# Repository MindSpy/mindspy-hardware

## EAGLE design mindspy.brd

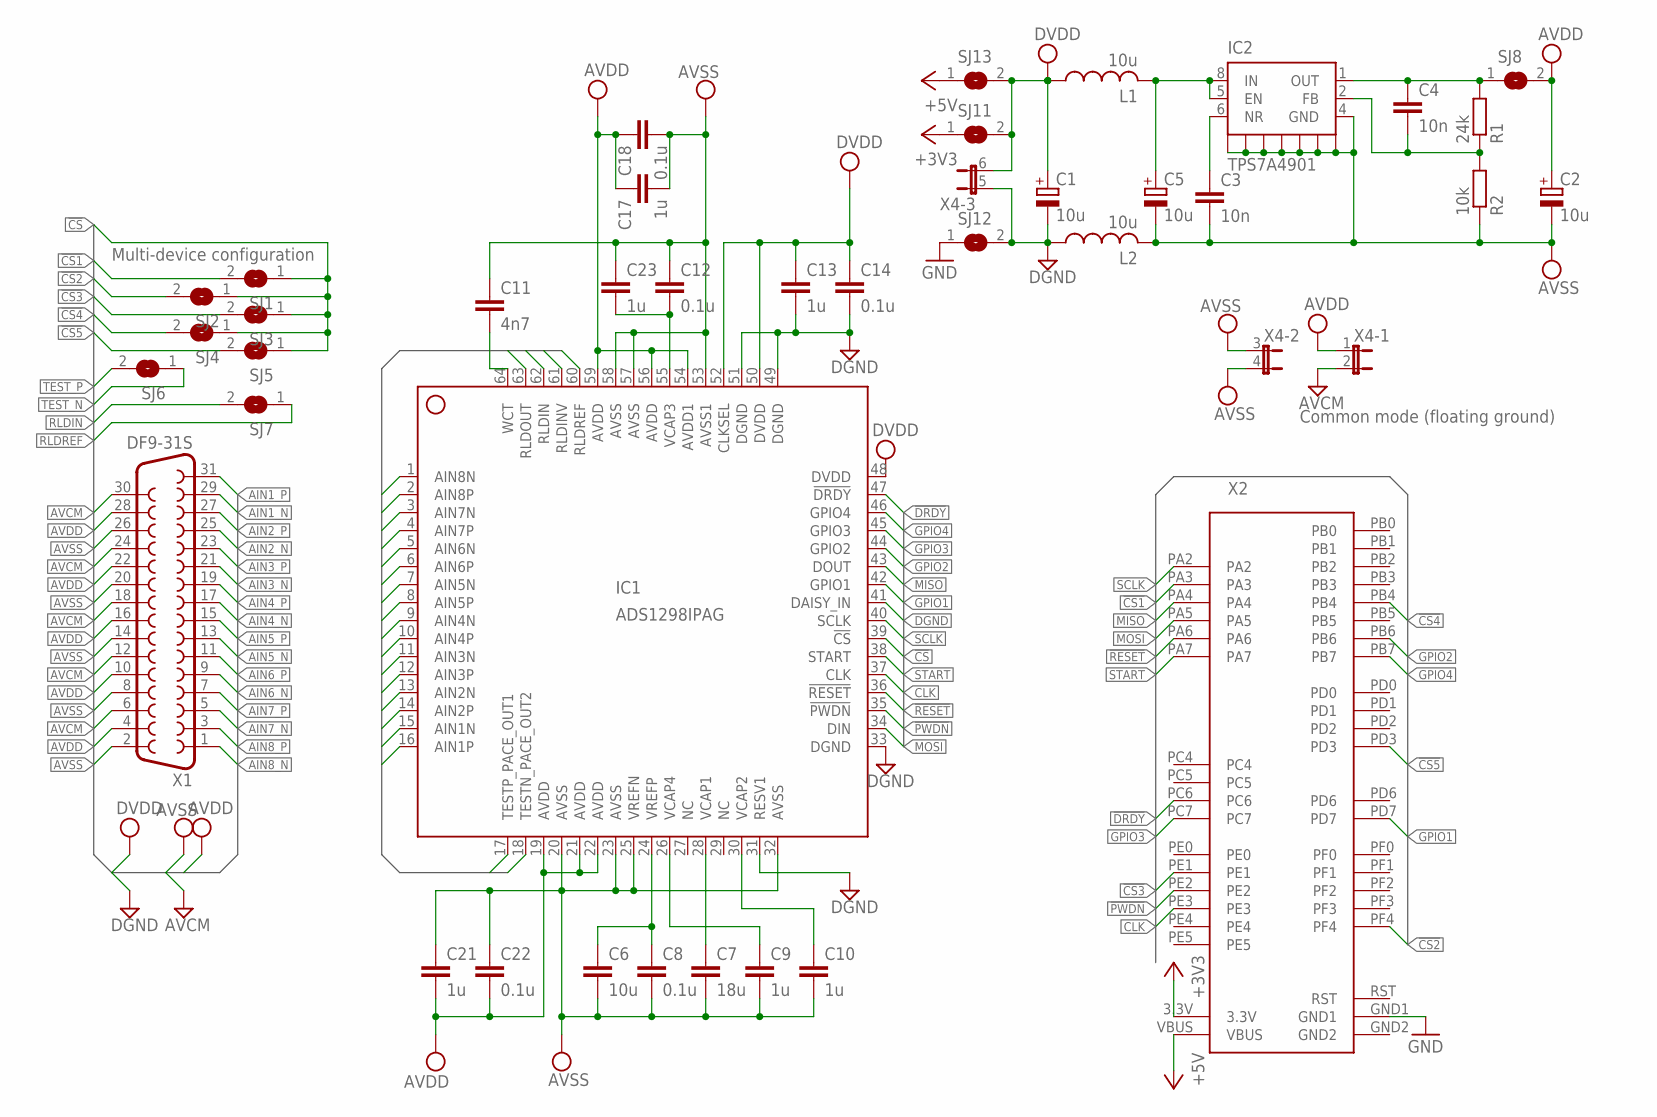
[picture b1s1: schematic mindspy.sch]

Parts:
C1, C2, C5: 10u; SMC_A
C3, C4: 10n; C0603
C6: 10u; C0805
C7: 18u; C0805
C8, C12, C14, C18, C22: 0.1u; C0402
C9, C10, C13, C17, C21, C23: 1u; C0402
C11: 4n7; C0402
IC1: ADS1298IPAG; LQFP64
IC2: TPS7A4901; MSOP08
L1, L2: 10u; L1210K
R1: 24k; R0402
R2: 10k; R0402
SJ1, SJ2, SJ3, SJ4, SJ5, SJ6, SJ7, SJ8, SJ11, SJ12, SJ13: SJ
X1: DF9-31S
X2: STELLARIS-LAUNCHPAD-HALF; LAUNCHPAD-L
X4: JP3QE; JP3Q

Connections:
!CS: IC1.39 (!CS), SJ1.1, SJ2.1, SJ3.1, SJ4.1, SJ5.1
!CS1: SJ1.2, X2.PA3
!CS2: SJ2.2, X2.PF4
!CS3: SJ3.2, X2.PE1
!CS4: SJ4.2, X2.PB4
!CS5: SJ5.2, X2.PD3
!DRDY: IC1.47 (!DRDY), X2.PC6
!PWDN: IC1.35 (!PWDN), X2.PE2
!RESET: IC1.36 (!RESET), X2.PA6
+3V3: SJ11.1, X2.3.3V
+5V: SJ13.1, X2.VBUS
AIN1_N: IC1.15 (AIN1N), X1.29
AIN1_P: IC1.16 (AIN1P), X1.31
AIN2_N: IC1.13 (AIN2N), X1.25
AIN2_P: IC1.14 (AIN2P), X1.27
AIN3_N: IC1.11 (AIN3N), X1.21
AIN3_P: IC1.12 (AIN3P), X1.23
AIN4_N: IC1.9 (AIN4N), X1.17
AIN4_P: IC1.10 (AIN4P), X1.19
AIN5_N: IC1.7 (AIN5N), X1.13
AIN5_P: IC1.8 (AIN5P), X1.15
AIN6_N: IC1.5 (AIN6N), X1.9
AIN6_P: IC1.6 (AIN6P), X1.11
AIN7_N: IC1.3 (AIN7N), X1.5
AIN7_P: IC1.4 (AIN7P), X1.7
AIN8_N: IC1.1 (AIN8N), X1.1
AIN8_P: IC1.2 (AIN8P), X1.3
AVCM: X1.6, X1.12, X1.18, X1.24, X1.30, X4.2
AVDD: C2.+, C17.1, C18.1, C21.2, C22.2, IC1.19 (AVDD), IC1.21 (AVDD), IC1.22 (AVDD), IC1.54 (AVDD1), IC1.56 (AVDD), IC1.59 (AVDD), SJ8.2, X1.4, X1.10, X1.16, X1.22, X1.28, X4.1
AVDD2: C4.1, IC2.1 (OUT), R1.2, SJ8.1
AVSS: C2.-, C3.2, C5.-, C6.2, C7.2, C8.2, C9.2, C10.2, C11.1, C12.1, C17.2, C18.2, C21.1, C22.1, C23.1, IC1.20 (AVSS), IC1.23 (AVSS), IC1.25 (VREFN), IC1.32 (AVSS), IC1.53 (AVSS1), IC1.57 (AVSS), IC1.58 (AVSS), IC2.4 (GND), IC2.NC@0 (GND), IC2.NC@1 (GND), IC2.NC@2 (GND), IC2.NC@3 (GND), IC2.NC@4 (GND), IC2.PWR@1 (GND), IC2.PWR@2 (GND), L2.2, R2.1, X1.2, X1.8, X1.14, X1.20, X1.26, X4.3 (1), X4.4 (2)
CLK: IC1.37 (CLK), X2.PE3
DGND: C1.-, C13.2, C14.2, IC1.31 (RESV1), IC1.33 (DGND), IC1.41 (DAISY_IN), IC1.49 (DGND), IC1.51 (DGND), L2.1, SJ12.2, X4.5 (1)
DVDD: C1.+, C13.1, C14.1, IC1.48 (DVDD), IC1.50 (DVDD), IC1.52 (CLKSEL), L1.1, SJ11.2, SJ13.2, X4.6 (2)
GND: SJ12.1, X2.GND1
GND2: X2.GND2
GPIO1: IC1.42 (GPIO1), X2.PD7
GPIO2: IC1.44 (GPIO2), X2.PB6
GPIO3: IC1.45 (GPIO3), X2.PC7
GPIO4: IC1.46 (GPIO4), X2.PB7
MISO: IC1.43 (DOUT), X2.PA4
MOSI: IC1.34 (DIN), X2.PA5
unnamed: C6.1, C8.1, IC1.24 (VREFP)
unnamed: C7.1, IC1.28 (VCAP1)
unnamed: C3.1, IC2.6 (NR)
unnamed: C9.1, IC1.26 (VCAP4)
unnamed: C10.1, IC1.30 (VCAP2)
unnamed: C12.2, C23.2, IC1.55 (VCAP3)
unnamed: C11.2, IC1.64 (WCT)
unnamed: C4.2, IC2.2 (FB), R1.1, R2.2
unnamed: C5.+, IC2.5 (EN), IC2.8 (IN), L1.2
RLDIN: IC1.62 (RLDIN), SJ7.2
RLDINV: IC1.61 (RLDINV)
RLDOUT: IC1.63 (RLDOUT)
RLDREF: IC1.60 (RLDREF), SJ7.1
RST: X2.RST
SCLK: IC1.40 (SCLK), X2.PA2
START: IC1.38 (START), X2.PA7
TEST_N: IC1.18 (TESTN_PACE_OUT2), SJ6.1
TEST_P: IC1.17 (TESTP_PACE_OUT1), SJ6.2

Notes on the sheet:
Common mode (floating ground)
Multi-device configuration

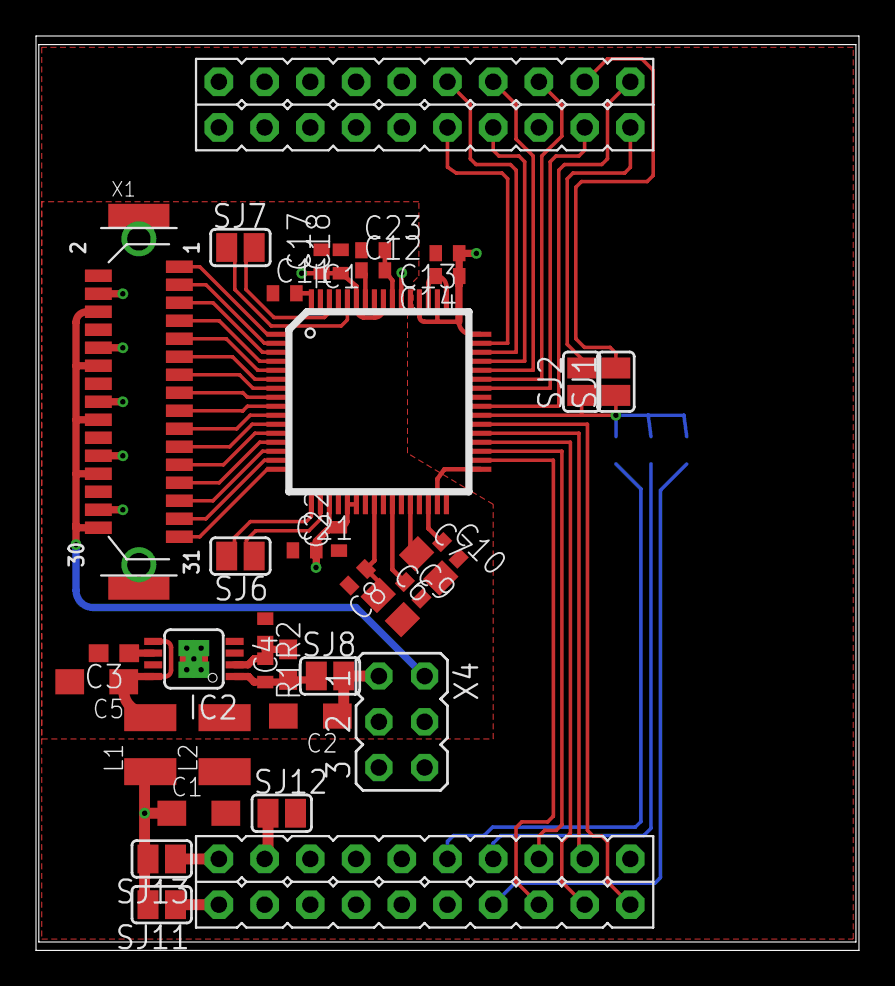
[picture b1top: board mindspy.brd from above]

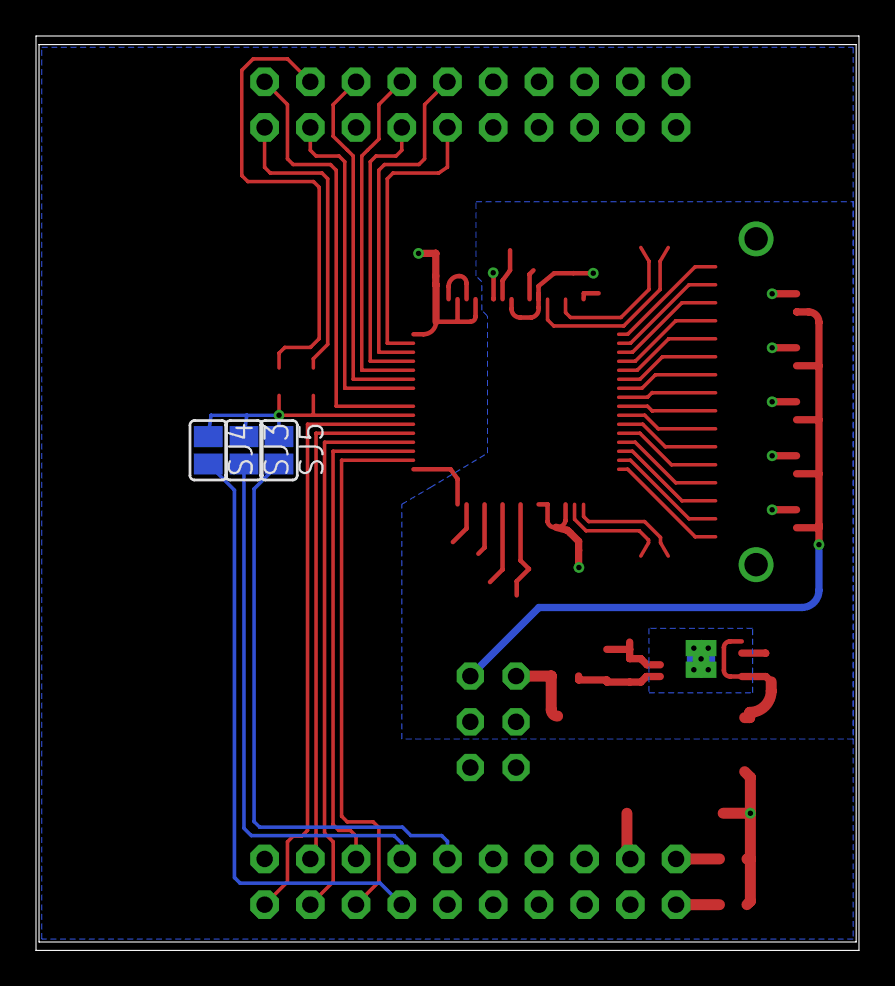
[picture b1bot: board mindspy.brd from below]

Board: 2 copper layers, 45.7 x 50.8 mm, 39 parts (3 on the bottom side), 56 nets.

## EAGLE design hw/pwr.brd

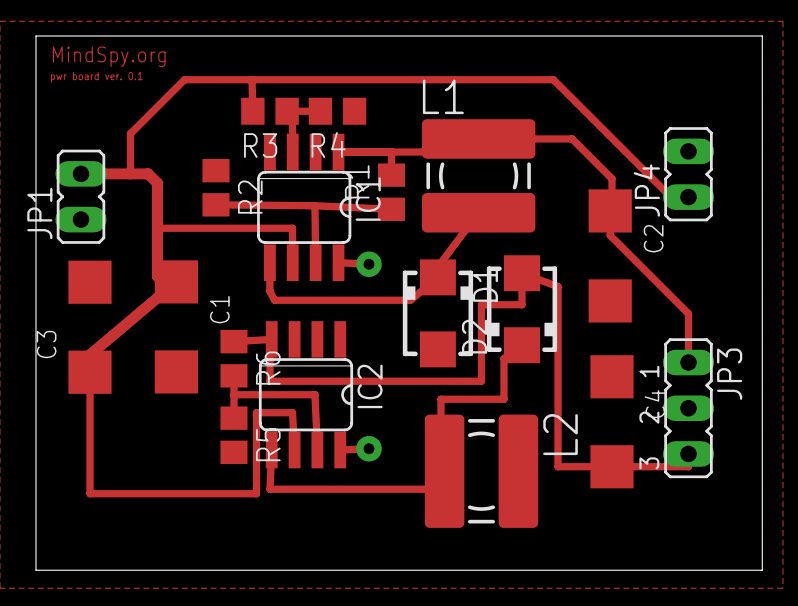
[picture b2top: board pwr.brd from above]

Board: 2 copper layers, 40.4 x 29.7 mm, 19 parts (0 on the bottom side), 10 nets.

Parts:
C1, C3: 33u; SMC_C
C2, C4: 100u; SMC_C
D1, D2: SS14; SMA
IC1, IC2: MAX640; SO08
JP1: BATT; JP1
JP3: ANAL; JP2
JP4: DIGI; JP1
L1, L2: POWER-CHOKE_WE-TPC
R1, R2, R3, R4, R5, R6: R0805

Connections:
+2V5: C2.+, IC1.1, JP3.1, L1.1, R1.2
-2V5: C4.-, D2.A, IC2.4, JP3.3, R6.1
GND: C1.-, C2.-, C3.-, C4.+, D1.A, IC1.4, IC2.1, IC2.3, JP1.1, JP3.2, JP4.2, L2.1, R2.1, R4.1, R5.2
unnamed: D1.C, IC1.5, L1.2
unnamed: D2.C, IC2.5, L2.2
unnamed: IC1.3, R3.1, R4.2
unnamed: IC1.7, R1.1, R2.2
unnamed: IC2.7, R5.1, R6.2
SHDN: IC1.8, IC2.8
VBAT: C1.+, C3.+, IC1.6, IC2.6, JP1.2, JP4.1, R3.2

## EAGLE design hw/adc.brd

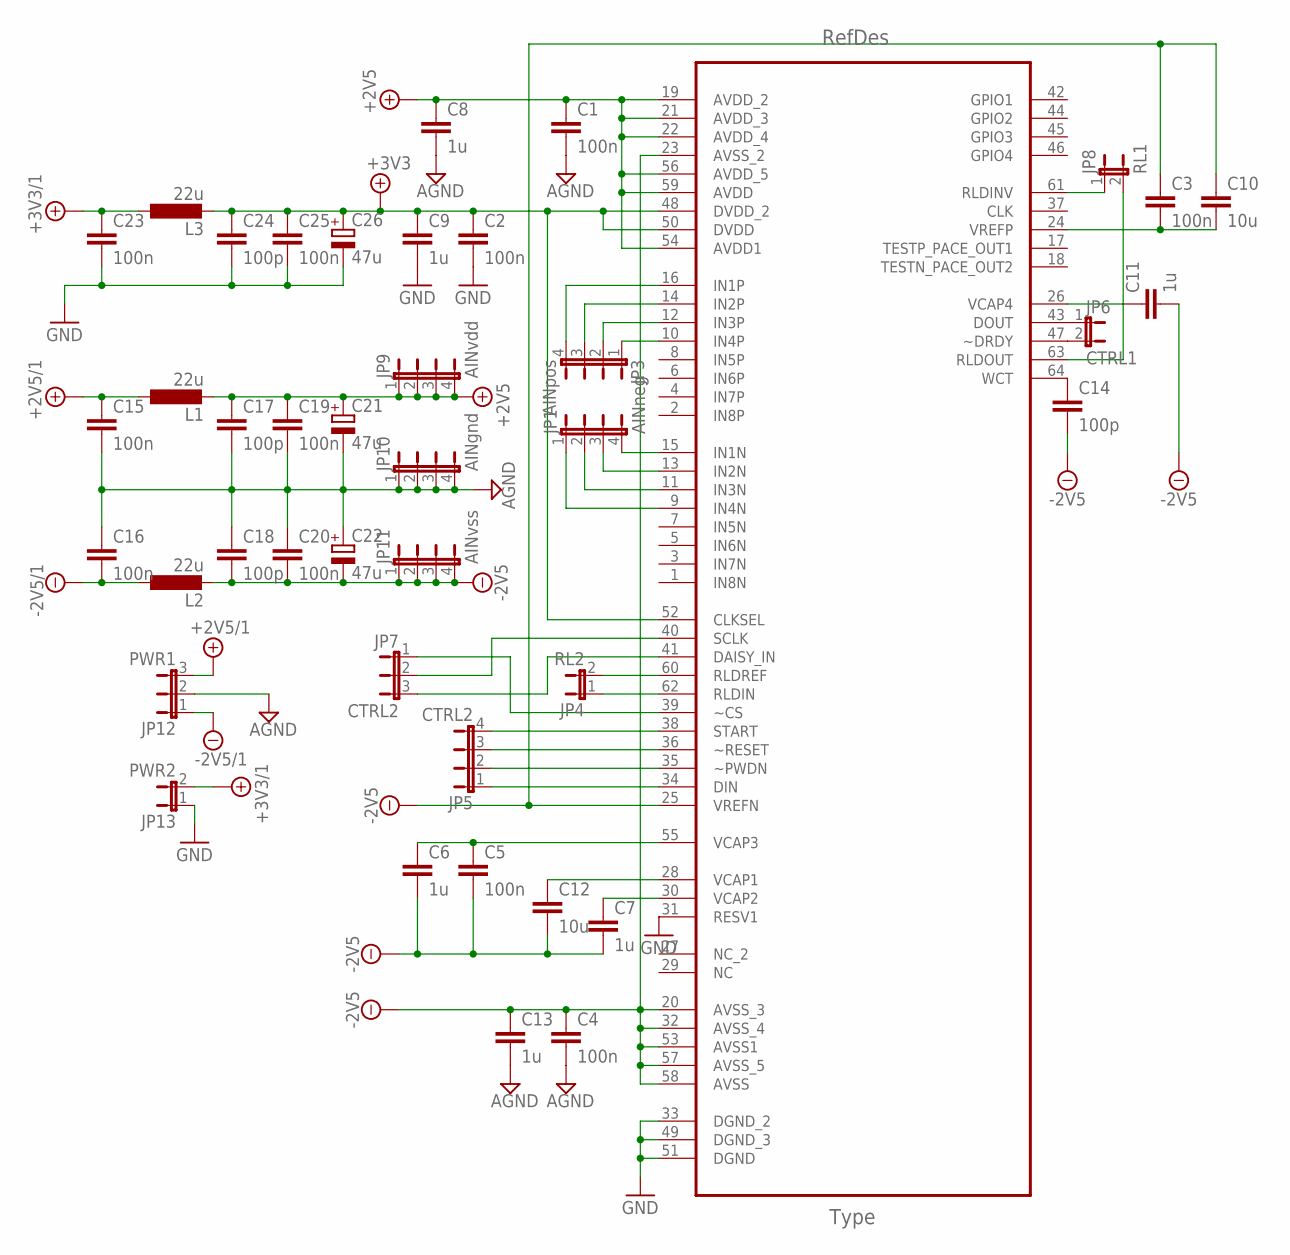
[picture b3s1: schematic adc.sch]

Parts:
C1, C2, C3, C4, C5, C15, C16, C19, C20, C23, C25: 100n; C0603K
C6, C7, C8, C9, C11, C13: 1u; C0805K
C10, C12: 10u; C0805K
C14, C17, C18, C24: 100p; C0603K
C21, C22, C26: 47u; SMC_C
JP1: AINneg; JP4
JP3: AINpos; JP4
JP4: RL2; JP1
JP5: CTRL2; JP4
JP6: CTRL1; JP1
JP7: CTRL2; JP2
JP8: RL1; JP1
JP9: AINvdd; JP4
JP10: AINgnd; JP4
JP11: AINvss; JP4
JP12: PWR1; JP2
JP13: PWR2; JP1
L1, L2, L3: 22u; L1812
U1: ADS1194CPAG; QFP50P1200X1200X120-64N

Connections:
+2V5: C1.1, C8.1, C17.1, C19.1, C21.+, JP9.1, JP9.2, JP9.3, JP9.4, L1.2, U1.19 (AVDD_2), U1.21 (AVDD_3), U1.22 (AVDD_4), U1.54 (AVDD1), U1.56 (AVDD_5), U1.59 (AVDD)
+2V5/1: C15.1, JP12.3, L1.1
+3V3: C2.1, C9.1, C24.1, C25.1, C26.+, L3.2, U1.48 (DVDD_2), U1.50 (DVDD), U1.52 (CLKSEL)
+3V3/1: C23.1, JP13.2, L3.1
-2V5: C3.1, C4.1, C5.2, C6.2, C7.2, C10.1, C11.2, C12.2, C13.1, C14.2, C18.2, C20.2, C22.-, JP11.1, JP11.2, JP11.3, JP11.4, L2.2, U1.20 (AVSS_3), U1.23 (AVSS_2), U1.25 (VREFN), U1.32 (AVSS_4), U1.53 (AVSS1), U1.57 (AVSS_5), U1.58 (AVSS)
-2V5/1: C16.2, JP12.1, L2.1
AGND: C1.2, C4.2, C8.2, C13.2, C15.2, C16.1, C17.2, C18.1, C19.2, C20.1, C21.-, C22.+, JP10.1, JP10.2, JP10.3, JP10.4, JP12.2
DAISY_IN: JP7.3, U1.41 (DAISY_IN)
DIN: JP5.1, U1.34 (DIN)
DOUT: JP6.1, U1.43 (DOUT)
GND: C2.2, C9.2, C23.2, C24.2, C25.2, C26.-, JP13.1, U1.31 (RESV1), U1.33 (DGND_2), U1.49 (DGND_3), U1.51 (DGND)
unnamed: C3.2, C10.2, U1.24 (VREFP)
unnamed: C5.1, C6.1, U1.55 (VCAP3)
unnamed: C7.1, U1.30 (VCAP2)
unnamed: C12.1, U1.28 (VCAP1)
unnamed: C11.1, U1.26 (VCAP4)
unnamed: JP1.4, U1.15 (IN1N)
unnamed: C14.1, U1.64 (WCT)
unnamed: JP1.3, U1.13 (IN2N)
unnamed: JP1.2, U1.11 (IN3N)
unnamed: JP1.1, U1.9 (IN4N)
unnamed: JP3.1, U1.10 (IN4P)
unnamed: JP3.4, U1.16 (IN1P)
unnamed: JP3.3, U1.14 (IN2P)
unnamed: JP3.2, U1.12 (IN3P)
unnamed: JP4.1, U1.62 (RLDIN)
unnamed: JP4.2, U1.60 (RLDREF)
unnamed: JP8.1, U1.61 (RLDINV)
unnamed: JP8.2, U1.63 (RLDOUT)
SCLK: JP7.2, U1.40 (SCLK)
START: JP5.4, U1.38 (START)
~CS: JP7.1, U1.39 (~CS)
~DRDY: JP6.2, U1.47 (~DRDY)
~PWDN: JP5.2, U1.35 (~PWDN)
~RESET: JP5.3, U1.36 (~RESET)

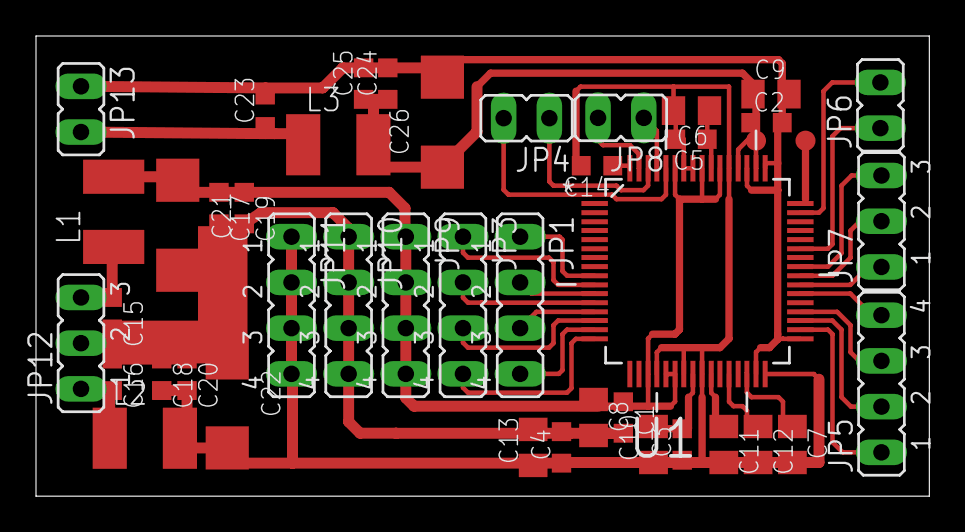
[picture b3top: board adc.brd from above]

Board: 2 copper layers, 49.6 x 25.6 mm, 42 parts (0 on the bottom side), 35 nets.

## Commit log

2012-04-10 Early stage
2012-04-14 Prepared for sex
2012-04-15 mingor changes and renames
2012-04-15 move to subdir.
2012-04-15 final updates to ADC board
2012-04-15 power supplies
2012-04-15 created power board
2012-04-15 minor changes to board desriptions
2012-04-15 Fix problems with polarity and route length and crossing as well
2012-04-28 Sargon rocks
2013-08-04 added stellaris shield
2013-08-08 Major modifications.
2013-08-08 higher res
2013-08-12 digital prat completed
2013-08-12 minor change
2013-08-23 move recent files to root and remove obsoleted files
2013-08-24 almost final
2013-08-24 errorneous previous commit
2013-08-26 fix urouted capacitors C7, C9 and C10
2013-08-27 use half-sized launchpad shield
2013-08-27 makefile for gerber and eps files
2013-08-27 ignore out dir
2013-08-27 add documentation circles for IC's
2013-08-27 decrease wire width
2013-08-27 refactor
2013-08-27 change packag for ADS1298 (HTQFP-64-PAP -> LQFP64)
2013-08-27 little fix
2013-08-28 add pads for RLD auxiliary input and rearrange wires
2013-08-28 refactor Makefile
2013-08-29 minor fixes
2013-08-29 finalization, fixes in layers
2013-08-30 update image
2013-09-03 refactro makefile
2013-09-03 adding gerber files
2013-09-03 remove dimension from text layer
2013-10-31 fix part values
2013-10-31 Major changes
    * placing improvements
    * labels on board
2013-11-01 little improvement in placing
2013-12-03 add panelizer option
2013-12-03 recent version of the prototype
2013-12-03 update images
2014-10-02 add dry electrode design
2014-10-05 electrode pin
2014-10-05 update pin drawing
2014-10-07 change sketch plane
2014-10-07 update render
2014-10-07 update PCB size to 1.5 mm
